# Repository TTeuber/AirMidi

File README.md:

# AirMidi

A battery-powered wireless MIDI interface: it gives any TRS MIDI device (or DIN, with an adapter) Bluetooth and Wi-Fi,
is set up from a browser or a phone, and updates itself over the air. This repo is its firmware, for an ESP32-C6 or
ESP32-S3 on a custom PCB in a 3D-printed box, and the apps that play it: one for Android phones and one for the Mac,
which sequences hardware synths through the box.

## Highlights

- **Six MIDI transports through one router**: TRS (31250 baud UART), BLE MIDI (peripheral and central), Network
  MIDI 2.0, RTP-MIDI, USB MIDI and an ESP-NOW link between two boxes. Everything is UMP (MIDI 2.0's packet format)
  inside, translated to and from MIDI 1.0 at the edges, with a per-output merge that never breaks a SysEx message.
- **Protocols built from their specs and tested against real implementations**: macOS's own Network MIDI 2.0 and
  RTP-MIDI drivers connect to the box; the RTP-MIDI recovery journal (RFC 6295) repairs lost packets; MIDI-CI
  Property Exchange reads a synth's controls over a 31250 baud cable and the web UI draws them.
- **A portable C11 core** (`lib/`, no ESP-IDF headers) with 17 suites of host tests under AddressSanitizer and
  UndefinedBehaviorSanitizer, including property tests (the journal through 30-50% packet loss).
- **Measured on the hardware, not assumed**: an audio interface cabled to the box's jacks puts both ends of every
  test on the Mac's clock, so latency and loss are measured one way, per transport. Every number below comes from
  those tests.
- **Safe updates**: signed images (RSA-3072), a self-test after each update and automatic rollback, core dumps
  from crashes; releases are built and signed in GitHub Actions.
- **Apps for phone and desktop** from one Flutter project: an Android app that sets the box up over Bluetooth and
  plays it as an MPE instrument, and a macOS app with a MIDI-only DAW for hardware synths, whose tracks know each
  synth's controls from what it sent over MIDI-CI.

## Hardware

The receiver PCB: a Seeed XIAO ESP32-C6 (or ESP32-S3) on headers, MIDI out through a TRS Type A jack, MIDI in
through a 6N138 optocoupler, a Li-ion cell with a TP4057 USB-C charger and a TPS63020 buck-boost to 3.3 V, a power
switch, a button and an LED. An ESP32-S3-DevKitC-1 serves as the second box for USB MIDI and the ESP-NOW link. The
board layer ([board-and-settings.md](docs/design/board-and-settings.md)) is the only code that names a GPIO.

**[hardware/](hardware)** has the schematic, the KiCad project, Gerbers, BOM and the printable enclosure, with the
board's revision history: the photo shows rev A, and rev B fixes what its bring-up found.

### The rev B panel

| button | tap | hold 2 s (its LED lights when you can let go) |
|---|---|---|
| BLE (blue) | Play mode: BLE + TRS | open the pairing window for a new phone (2 min) |
| NET (green) | Network mode | check GitHub for a newer release, install it |
| STP (yellow) | Setup mode; again: back to the mode before | MIDI-CI scan of the device on the jacks |
| PWR (red) | the four LEDs show the battery for 3 s | off (deep sleep); hold 1 s to start again |

Two quick taps on any button: all notes off, at the second tap. A hold that needs the other mode switches first
(with the restart a BLE change takes), then does its job. The LEDs: BLE flashes once a second while advertising, is
on when connected (dark flicker on MIDI), blinks fast while the pairing window for a new phone is open (it closes
once a phone is added; the one after power-on also closes when a trusted phone connects, and never blinks over a
connection); NET blinks while joining,
is dim when joined and on with a session, blinks fast while checking or installing, then shows the result (on: up
to date, three flashes: failed); STP double-flashes in Setup, blinks dim during a scan, then on (found) or three
flashes (nothing); PWR is on, triple-flashes on a low cell. The battery bar is a quarter per LED; with the switch
off on USB (no cell reading) all four blink.

## Features

- **TRS <-> BLE MIDI**, up to two BLE centrals at once. One way through the box: BLE -> TRS 8.4 ms median,
  TRS -> BLE 9.5 ms, nothing lost in the hardware tests.
- **Wi-Fi modes**: Play (Wi-Fi off), Network (joins stored networks, reachable as `<name>.local`), Setup (its own
  access point). A long press switches mode, an 8 s press opens Setup, a double press sends all notes off. Rev B
  has a panel instead: a button per mode (BLE, NET, STP) and PWR, each with an LED over it (below).
- **Web UI** at `http://<name>.local`: live traffic per port, battery, signal, settings, Wi-Fi networks, firmware
  updates. Plain JS, no framework, 18 KB, built into the firmware.
- **Network MIDI 2.0** host (UDP, `_midi2._udp`): macOS connects to it natively. FEC, retransmit and in-order
  delivery over Wi-Fi: 0 of 600 lost at 5 ms spacing, 6.7 ms median Mac -> TRS, 4.2 ms back.
- **MIDI-CI over TRS**: Discovery and Property Exchange with the synth on the jacks (a full read in under a second
  at 31250 baud, ~50 ms for a known device from the flash cache). The play page draws the synth's own faders,
  pickers and toggles from its control list (M2-117); synths without MIDI-CI get the same from an uploaded JSON
  profile. A MIDI-CI host behind the box reaches the synth through it: macOS finds it over Network MIDI 2.0.
- **RTP-MIDI** (AppleMIDI, `_apple-midi._udp`) for clients without Network MIDI 2.0: lost packets repaired from the
  recovery journal, sessions taken back after the box restarts. With macOS's driver: 0 of 600 lost each way at 5 ms
  spacing, 7.3 / 5.5 ms median.
- **BLE central**: the box connects by itself to a BLE MIDI keyboard or controller (any, by name or by address).
  13.0 ms median keyboard -> TRS.
- **USB MIDI** on the S3: a class-compliant USB MIDI device named after the box, with a serial console beside it.
- **ESP-NOW link**: two boxes pass MIDI radio to radio, no router, and find each other's Wi-Fi channel by
  themselves. TRS -> box -> ESP-NOW -> box -> USB in 3.8 ms median, nothing lost.
- **Updates**: upload in the browser, fetch the latest GitHub release, or send it over BLE when the box is not on
  Wi-Fi. Only signed images install; a new image must pass a self-test or the box rolls back.
- **Battery**: gauge, low warning, and all notes off plus deep sleep when the cell is empty.

## Web UI

## Apps

One Flutter project ([app/](app)) builds two apps over shared code: the box pages, the BLE and Wi-Fi links, and the
synth page drawn from the synth's MIDI-CI control list.

**Phone** (Android; [plan and decisions](docs/app.md)):

- Finds the box over Bluetooth or Wi-Fi and sets it up: mode, Wi-Fi networks from the box's own scan, trusted
  phones. Setup goes over a BLE GATT service that carries the same JSON API as the web UI's HTTP.
- Plays the synth on the box's TRS jacks: pedal-steel strips (each finger bends its own note, one MPE channel per
  strip), keys, or drum pads; over BLE MIDI, the box's WebSocket, or Android's MIDI service straight to a computer.
- The synth page: envelopes, a cutoff and resonance pad, wave pickers and faders, built from the controls daisy_synth
  ([devices/daisy_synth](devices/daisy_synth)) describes over MIDI-CI.

**Desktop** (macOS now, Windows and Linux later; [plan](docs/desktop.md), [DAW design](docs/daw.md)):

- The computer's MIDI ports through libremidi over FFI (`app/packages/midi_engine`), a router between them, and the
  box's play view: the synth's controls over the keys.
- A MIDI-only DAW for hardware: MIDI clips in a piano roll with controller lanes and ramps, MPE takes with each
  note's own bend, pressure and timbre, and step-sequencer patterns with velocity, gate, probability, nudge, repeats
  and parameter locks. Records from any input, MPE included.
- Each track keeps its synth's MIDI-CI control list, so lanes and locks have the synth's own names and units. It also
  keeps the synth's program, bank and settings, which can be read back through the box. All of it is sent before
  play, so the song sounds the same on the next day.
- Click and count-in, latency offsets per port, projects saved as JSON every few seconds, Standard MIDI File import
  and export.

## How it is tested

- **Host tests** (`test/`): the portable core under ASan + UBSan, with randomized round trips and property tests.
- **App tests** (`app/test`, `fvm flutter test`): the strips, MPE and BLE MIDI packing, the router, and the DAW (editing,
  timing, files, recording, the player against a fake MIDI engine).
- **CI** (`.github/workflows/ci.yml`): host tests, the clang-format check, the firmware for every board, and the
  app's analyzer, tests and Android and Mac release builds on every push. `tools/check.sh` runs the same steps locally. Tagging `vX.Y.Z` builds, signs and publishes a release.
- **Hardware in the loop** (`tools/hil/`): Python and Swift tools on the Mac drive the box and an Arturia AudioFuse
  wired to its jacks. Their first runs found real bugs; each one is written up in [docs/design](docs/design).

| Test | Checks |
|---|---|
| `bridge_test.py` | TRS <-> BLE both ways: notes, CCs on all 16 channels, clock, long SysEx, bursts, two sources merged (15) |
| `ota_test.py`, `release_test.py`, `ble_ota_test.py` | unsigned, corrupted and wrongly signed images refused; good ones installed over Wi-Fi, from a release and over BLE; rollback after a failed self-test or a crash (13, 8, 9) |
| `web_test.py`, `ws_test.py` | the web API, and MIDI between the page and the jacks over WebSocket (14) |
| `ci_test.py`, `mac_ci_test.py` | MIDI-CI against a stand-in synth on the Mac, and macOS's own MIDI-CI through the box (21, 12) |
| `resume_test.py`, `rtp_test.py` | Network MIDI 2.0 and RTP-MIDI against macOS's drivers: loss, latency, box restarts (14, 13) |
| `central_test.py` | the box as BLE central against a BLE MIDI stand-in on the Mac (14) |
| `usb_test.py`, `espnow_test.py` | USB MIDI against BLE, and two boxes linked over ESP-NOW (9) |
| `latency.py`, `sleep_test.py` | one-way latency per path, MIDI through each power mode |

## Design notes

One note per module, with the reasoning, the alternatives considered and what the hardware tests found:

- [core.md](docs/design/core.md): UMP, MIDI 1.0 parsing and encoding, MIDI 1.0 <-> 2.0 translation
- [transports.md](docs/design/transports.md): the bus and merge, TRS, BLE MIDI, BLE central, USB MIDI, ESP-NOW, power
- [network-midi.md](docs/design/network-midi.md): Network MIDI 2.0
- [rtp-midi.md](docs/design/rtp-midi.md): RTP-MIDI, the recovery journal, and what macOS needed
- [midi-ci.md](docs/design/midi-ci.md): MIDI-CI Discovery and Property Exchange, the generated play page
- [ota.md](docs/design/ota.md): flash layout, signed updates, self-test and rollback, releases
- [board-and-settings.md](docs/design/board-and-settings.md): the board layer and the settings store
- [config-over-ble.md](docs/design/config-over-ble.md): one JSON API for HTTP and BLE, trusted phones, Wi-Fi setup from a phone
- [testing.md](docs/design/testing.md): the test rig and CI
- [measurements.md](docs/measurements.md): every number in this README, with its method
- [plan.md](docs/plan.md): the development plan and a decision log of every choice and measured result
- [app.md](docs/app.md): the Android app (`app/`): plan, phases and its decision log
- [desktop.md](docs/desktop.md): the desktop app (plan): MIDI engine, router, who keeps time; [daw.md](docs/daw.md): the DAW
- [system](docs/system/README.md): how the box, the app and future instruments fit together: tiers, links, the instrument checklist

## Layout

```
lib/        portable C11 core, no ESP-IDF headers         docs/design/  one note per module
test/       host unit tests for lib/ (Unity)              tools/hil/    hardware-in-the-loop tools for the Mac
firmware/   ESP-IDF project (C6 and S3)                   spikes/       early experiments, results in the plan
web/        the web UI (HTML/CSS/JS, gzipped into the firmware)
devices/    MIDI-CI device side: the Mac stand-in (CoreMIDI) and daisy_synth, the demo synth
hardware/   the receiver PCB and enclosure: schematic, KiCad project, Gerbers, BOM, STL
app/        Flutter: the Android app, the macOS app with the DAW, and the code they share
```

## Build

```sh
tools/check.sh                    # what CI runs: host tests, clang-format check, firmware for every board
firmware/build.sh c6 flash        # build and flash the C6 board (s3: XIAO S3 on rev A, s3b: on rev B, s3kit: S3 dev kit)
cd app && fvm flutter test        # the apps' tests (Flutter pinned in app/.fvmrc)
fvm flutter build apk --release   # the Android app (fvm flutter build macos --release for the Mac)
```

Needs ESP-IDF v5.5.5 or later in the v5.5 series (`IDF_PATH`, default `~/Developer/esp-idf`), CMake, and `uv` (for
the pinned clang-format and the Python test tools). Each [release](https://github.com/TTeuber/AirMidi/releases) has
the update image per board and a zip for a first install over USB (`esptool.py write_flash @flash_args`).

## License

The firmware, software and documentation are MIT ([LICENSE](LICENSE)); the hardware in `hardware/` is
CERN-OHL-P-2.0 ([hardware/LICENSE](hardware/LICENSE)), the permissive open hardware licence. Two bundled third-party
parts keep their own licenses: the Unity test framework in `test/unity/` (MIT,
[test/unity/LICENSE.txt](test/unity/LICENSE.txt)) and the Geist font in `web/` (SIL Open Font License 1.1,
[web/OFL-Geist.txt](web/OFL-Geist.txt)).

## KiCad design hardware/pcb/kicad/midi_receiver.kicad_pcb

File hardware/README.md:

# Hardware: the AirMidi receiver, rev B

A 72 x 46 mm two-layer board for a Seeed XIAO ESP32-C6 or ESP32-S3, in an 80 x 52 x 27 mm 3D-printed box. The
photo shows rev A, the board the firmware was developed and tested on; this folder is rev B, which fixes rev A's
mistakes (see [Revisions](#revisions)).

The schematic, board and enclosure are generated from code (a Python circuit description, a layout file and a
build123d enclosure script) in a separate design workspace. The files here are that workspace's outputs, copied in by
an export script: they are replaced on every export, so edit the design there, not here.

## What's here

| Path | Contents |
|---|---|
| [pcb/schematic.pdf](pcb/schematic.pdf) | the schematic |
| [pcb/board.pdf](pcb/board.pdf), [pcb/board_3d.png](pcb/board_3d.png), [pcb/board_3d_bottom.png](pcb/board_3d_bottom.png) | the board: copper, silkscreen, 3D renders |
| [pcb/erc.txt](pcb/erc.txt), [pcb/drc.txt](pcb/drc.txt) | electrical and design rule checks: 0 errors, 0 unconnected, schematic and board in step |
| [pcb/kicad/](pcb/kicad) | the KiCad 10 project, with the symbols, footprints and 3D models it needs beyond KiCad's own library in `kicad/lib/` |
| [fab/midi_receiver_gerbers.zip](fab/midi_receiver_gerbers.zip) | Gerbers and Excellon drill file, as uploaded to JLCPCB (any 2-layer fab takes them) |
| [fab/bom.csv](fab/bom.csv) | every part, including the ones without a footprint (cell, screws) |
| [fab/bom_jlcpcb.csv](fab/bom_jlcpcb.csv), [fab/cpl_jlcpcb.csv](fab/cpl_jlcpcb.csv) | JLCPCB's BOM and placement formats |
| [enclosure/base.stl](enclosure/base.stl), [enclosure/lid.stl](enclosure/lid.stl) | the box, ready to slice (GitHub shows them in 3D); STEP files beside them |
| [enclosure/assembly_views.png](enclosure/assembly_views.png) | the board and every part inside the closed box |

The 3D models of the LCSC parts (TRS jacks, optocoupler, slide switch) are not included, as their license terms are
unclear; KiCad's 3D viewer shows those parts as bare footprints. The renders above were made with them.

## Circuit

```
phone / DAW  <~~ BLE MIDI, Wi-Fi ~~>  XIAO ESP32-C6 / S3  --UART TX--> 10R / 33R current loop --> J2 TRS out --> synth
                                            ^
keyboard --> J3 TRS in --> 220R + 1N4148 --> 6N138 optocoupler, 1k pull-up --UART RX

USB-C --> TP4057 charger module --> Li-ion cell 1050 mAh (J1) --> SW1 --> TPS63020 buck-boost --> 3.3 V --> XIAO 3V3
                                                                       '--> 100k / 100k divider --> A0 (battery gauge)
```

- **MIDI out**: a 3.3 V current loop (10 ohm on the source side, 33 ohm on the data side) to a TRS Type A jack:
  tip = DIN pin 5, ring = DIN pin 4.
- **MIDI in**: the MIDI spec's opto-isolated input with a 6N138: 220 ohm and a reverse 1N4148 on its LED, 1k pull-up
  to 3.3 V on its output.
- **Power**: the cell feeds a TP4057 charger module (USB-C, 500 mA) and, through the power switch, a TPS63020
  buck-boost that makes 3.3 V over the cell's whole range. Both are modules on header pins. The XIAO runs from its
  3V3 pin, so the switch must be off before the XIAO's own USB is plugged in.
- **User interface**: a status LED and a 13 mm tactile button that reach through the lid.

| Signal | XIAO pin | C6 GPIO | S3 GPIO |
|---|---|---|---|
| MIDI TX -> J2 | D6 | 16 | 43 |
| MIDI RX <- J3 | D7 | 17 | 44 |
| Battery sense | A0 | 0 | 1 |
| Status LED | D1 | 1 | 2 |
| Button (to GND) | D2 | 2 | 3 |

## Enclosure

Two parts that print without supports: the base, with a pocket for the cell under the board, and a flat lid. Four
M3 x 20 screws go through the lid and the board into the base. The jacks sit flush in the front wall, the power
switch's handle comes through a slot in the right wall, and both USB-C ports (charging, and the XIAO for flashing)
face the back.

## Measured on rev A

| What | Result |
|---|---|
| MIDI loopback J2 -> J3 at 31250 baud | 30208 of 30208 bytes correct; still clean at 62500 baud (2x headroom) |
| XIAO current, BLE connected | 40-50 mA |
| Battery gauge vs a multimeter | 3.726 V vs 3.74 V |
| Radio, ceramic antenna, box closed | BLE advertisement at the Mac -42 dBm, connection -50 dBm |
| Latency and loss through the box | in the firmware's [measurements](../docs/measurements.md) |

## Revisions

**Rev A** (ordered 2026-09-22, built 2026-10-03; the board in the photo):

- **Battery connector reversed.** JST-PH battery plugs have no standard polarity: the footprint put + on pin 1, but
  the cell's plug has its red lead on pin 2. Plugged in for the first time, the reversed cell destroyed the TP4057
  charger module. Lesson: check every cell's lead colours against the footprint's pad numbers before ordering.
- **Garbage on MIDI OUT at reset.** D6/D7 are the module's UART0 pins, and the chip's ROM bootloader prints its boot
  banner on UART0 TX before any firmware runs, which a synth reads as random MIDI messages. Fixed without a new
  board: one eFuse (`UART_PRINT_CONTROL`) silences the ROM output, and the firmware drives MIDI from UART1 routed to
  those pins ([board-and-settings.md](../docs/design/board-and-settings.md)).
- **An ESP32-C6 instead of the planned S3** (the S3s were back-ordered). The XIAO modules share a pinout, so the
  board did not change; the firmware's board layer maps the GPIOs. (The footprint keeps its `XIAO_ESP32S3` name.)
- **Enclosure too low** for the leads the hand-soldered parts leave under the board.

**Rev B** (this folder; not built yet): the cell connector's pins swapped to match the cell; the enclosure with 6 mm
under the board for those leads (27 mm tall overall), the cell pocket moved against the jack wall, and a gap in a
rib for the cell's lead.

## License

[CERN-OHL-P-2.0](LICENSE) (CERN Open Hardware Licence, permissive), for everything in this folder. The firmware and
the rest of the repository are MIT.

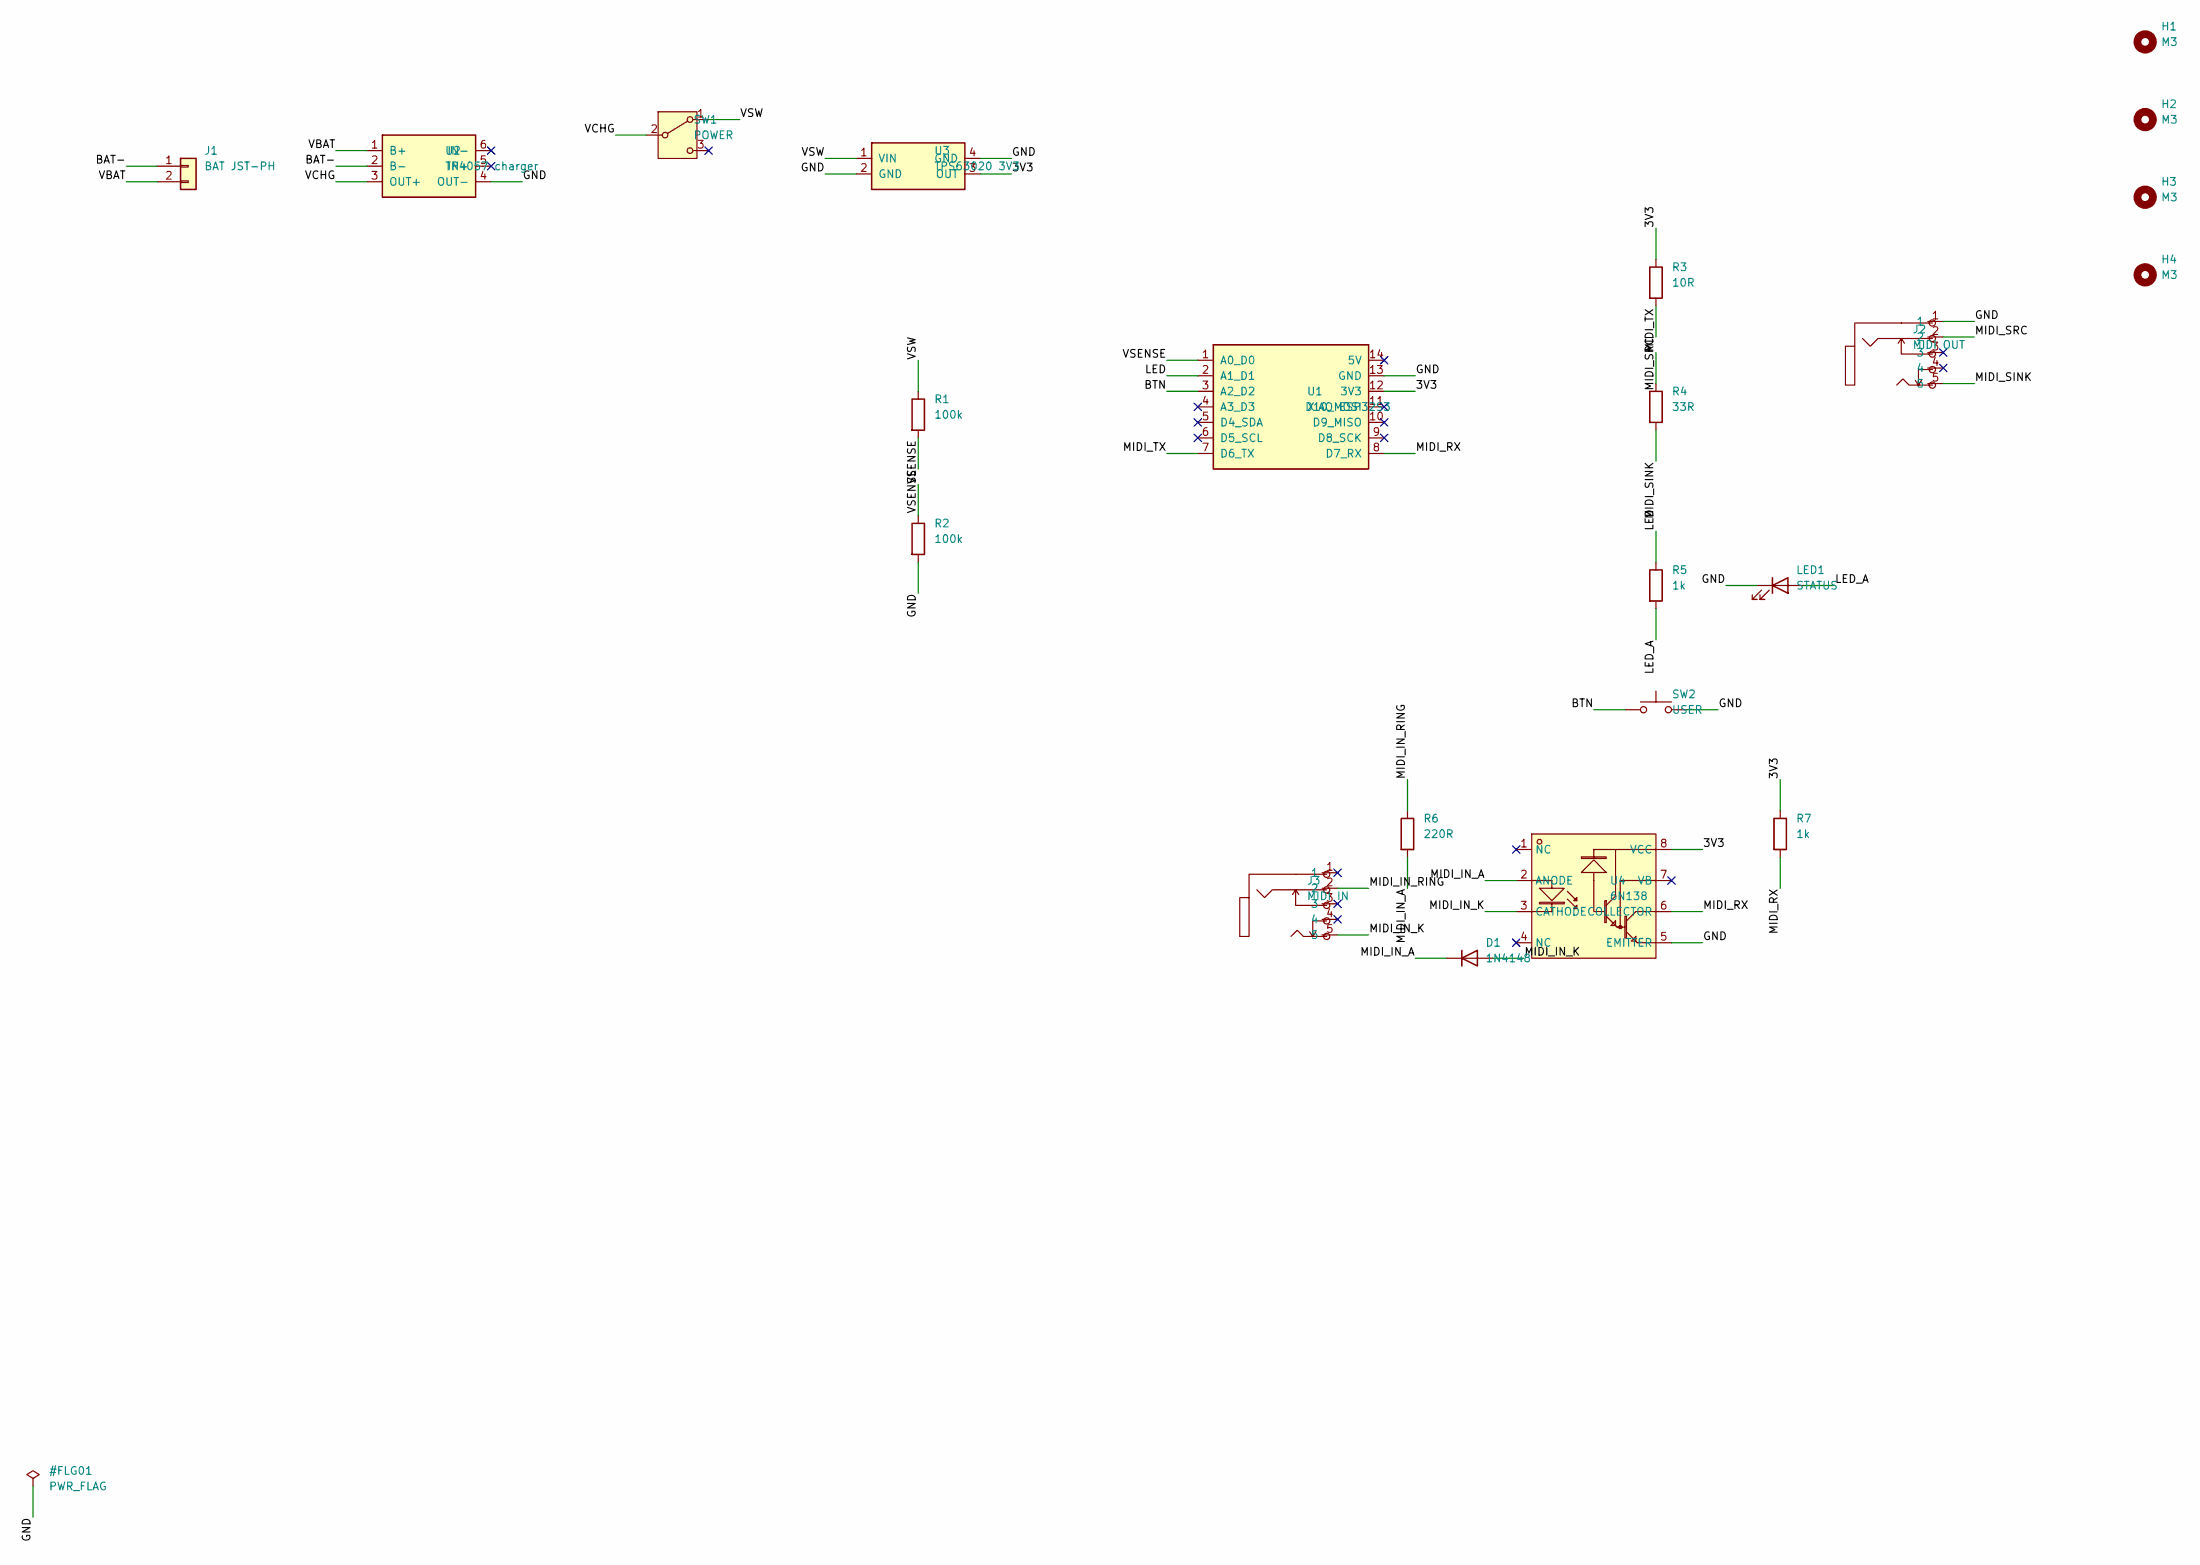
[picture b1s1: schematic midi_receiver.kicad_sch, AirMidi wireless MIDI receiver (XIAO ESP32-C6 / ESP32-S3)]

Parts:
D1: 1N4148; D_DO-35_SOD27_P7.62mm_Horizontal
H1, H2, H3, H4: M3; MountingHole_3.2mm_M3
J1: BAT JST-PH; JST_PH_S2B-PH-K_1x02_P2.00mm_Horizontal
J2: MIDI OUT; AUDIO-TH_PJ307C
J3: MIDI IN; AUDIO-TH_PJ307C
LED1: STATUS; LED_D3.0mm
R1, R2: 100k; R_Axial_DIN0207_L6.3mm_D2.5mm_P7.62mm_Horizontal
R3: 10R; R_Axial_DIN0207_L6.3mm_D2.5mm_P7.62mm_Horizontal
R4: 33R; R_Axial_DIN0207_L6.3mm_D2.5mm_P7.62mm_Horizontal
R5, R7: 1k; R_Axial_DIN0207_L6.3mm_D2.5mm_P7.62mm_Horizontal
R6: 220R; R_Axial_DIN0207_L6.3mm_D2.5mm_P7.62mm_Horizontal
SW1: POWER; SW-TH_3P-P4.80_HX-SS12D10G6-WJ
SW2: USER; SW_PUSH_6mm_H13mm
U1: XIAO ESP32S3; XIAO_ESP32S3
U2: TP4057 charger; TP4057_Module
U3: TPS63020 3V3; TPS63020_Module
U4: 6N138; DIP-8_W7.62mm_Socket

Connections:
/3V3: R3.1, R7.1, U1.12 (3V3), U3.3 (OUT), U4.8 (VCC)
/BAT-: J1.1, U2.2 (B-)
/BTN: SW2.1, U1.3 (A2_D2)
/GND: J2.1, LED1.1 (K), R2.2, SW2.2, U1.13 (GND), U2.4 (OUT-), U3.2 (GND), U3.4 (GND), U4.5 (EMITTER)
/LED: R5.1, U1.2 (A1_D1)
/LED_A: LED1.2 (A), R5.2
/MIDI_IN_A: D1.1 (K), R6.2, U4.2 (ANODE)
/MIDI_IN_K: D1.2 (A), J3.5, U4.3 (CATHODE)
/MIDI_IN_RING: J3.2, R6.1
/MIDI_RX: R7.2, U1.8 (D7_RX), U4.6 (COLLECTOR)
/MIDI_SINK: J2.5, R4.2
/MIDI_SRC: J2.2, R3.2
/MIDI_TX: R4.1, U1.7 (D6_TX)
/VBAT: J1.2, U2.1 (B+)
/VCHG: SW1.2 (B), U2.3 (OUT+)
/VSENSE: R1.2, R2.1, U1.1 (A0_D0)
/VSW: R1.1, SW1.1 (A), U3.1 (VIN)

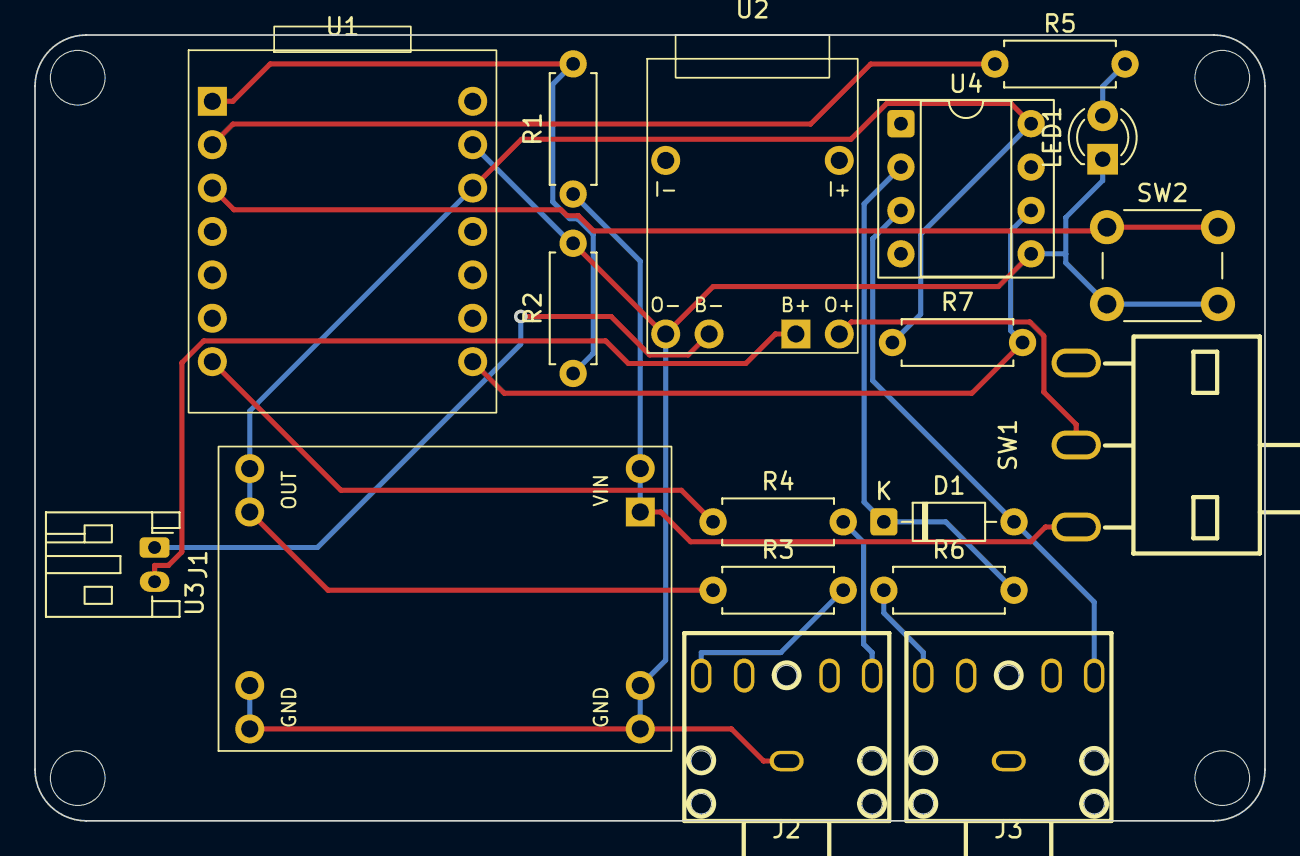
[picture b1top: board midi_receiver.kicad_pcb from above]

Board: 2 copper layers, 72.0 x 46.0 mm, 22 parts (0 on the bottom side), 17 nets.

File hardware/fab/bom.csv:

qty,refs,description,MPN,LCSC
1,U1,Seeed XIAO ESP32S3 soldered straight onto the board on its male headers (no sockets),XIAO ESP32S3,C2913204
1,U2,"TP4057 USB-C Li-ion charger module with protection, 12.1 x 17 mm, soldered on header stubs",TP4057 USB-C module,
1,U3,"TPS63020 buck-boost module, 1.8-5.5 V in, 3.3 V out, 17.6 x 26.3 mm, soldered on header stubs",TPS63020 module,
1,J1,"JST S2B-PH-K-S, 2-pin PH 2.0 mm side-entry socket (Li-ion cell plug)",S2B-PH-K-S(LF)(SN),C173752
2,J2 J3,"3.5 mm stereo jack, right angle PCB mount, 5 pins (PJ-307C) for TRS MIDI",PJ-307C,C16684
1,U4,"6N138 darlington optocoupler, DIP-8, in a socket (MIDI in)",6N138,C3001991
1,SW1,"SPDT slide switch, right angle (bent pins), 4.8 mm pitch, 12.7 x 6.2 x 6.5 body, 6 mm handle (SS12D10G6-WJ)",SS12D10G6-WJ,C7431059
1,SW2,"6 mm tactile button, 13 mm tall round stem (user button through a flat lid)",KH-6X6X13H-TJ,C2837523
1,D1,"1N4148 small signal diode, DO-35, lying flat on 7.62 mm (MIDI in reverse protection)",1N4148,
1,LED1,"3 mm LED, green (BLE status)",3A4GUD,C52034646
2,R1 R2,"100 kOhm 1/4 W resistor, flat (battery-sense divider)",,
1,R3,"10 Ohm 1/4 W resistor, flat (MIDI out source side)",,
1,R4,"33 Ohm 1/4 W resistor, flat (MIDI out data side)",,
2,R5 R7,"1 kOhm 1/4 W resistor, flat (LED series)",,
1,R6,"220 Ohm 1/4 W resistor, flat (MIDI in LED series)",,
4,H1 H2 H3 H4,M3 mounting hole,,
1,,"EEMB LP553454 Li-Po cell, 3.7 V 1050 mAh, 54x34x5 mm, JST-PH 2.0 plug, built-in protection (PCM)",LP553454,
7,,1x2 2.54 mm pin header (footswitch leads),,
1,,"DIP-8 IC socket, 7.62 mm",DS1009-08AT1NX-0A2,C72124
4,,M3 x 20 mm pan head screw (receiver lid through the boss and PCB into the base standoff),,

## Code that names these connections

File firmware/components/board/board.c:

#include "board.h"

#include <stdio.h>

#include "driver/gpio.h"
#include "esp_mac.h"
#include "sdkconfig.h"

#if CONFIG_AIRMIDI_BOARD_XIAO_C6
static const board_t the_board = {
    .name = "receiver rev A + XIAO ESP32-C6",
    .midi_tx = GPIO_NUM_16,
    .midi_rx = GPIO_NUM_17,
    .led = GPIO_NUM_1,
    .button = GPIO_NUM_2,
    .batt_adc_unit = ADC_UNIT_1,
    .batt_adc_channel = ADC_CHANNEL_0,  // GPIO0
    .batt_offset_mv = 14,               // board #1: calibrated ADC read 14 mV under the meter (2026-10-05)
};
// Inside the XIAO C6 module: GPIO3 low powers the RF switch, GPIO14 low selects the ceramic antenna (high = the
// U.FL connector, measured ~20 dB weaker with nothing plugged in).
#define RF_SWITCH_EN GPIO_NUM_3
#define ANT_SELECT GPIO_NUM_14
#elif CONFIG_AIRMIDI_BOARD_XIAO_S3
static const board_t the_board = {
    .name = "receiver rev A + XIAO ESP32-S3",
    .midi_tx = GPIO_NUM_43,
    .midi_rx = GPIO_NUM_44,
    .led = GPIO_NUM_2,
    .button = GPIO_NUM_3,
    .batt_adc_unit = ADC_UNIT_1,
    .batt_adc_channel = ADC_CHANNEL_0,  // GPIO1
};
#elif CONFIG_AIRMIDI_BOARD_XIAO_S3_B
// pcb/midi_receiver/circuit.py PANEL in the design workspace: LEDs A1 A3 SDA SCL, buttons SCK MISO MOSI A2.
static const board_t the_board = {
    .name = "receiver rev B + XIAO ESP32-S3",
    .midi_tx = GPIO_NUM_43,
    .midi_rx = GPIO_NUM_44,  // H11L1 output, 270R pull-up
    .led = GPIO_NUM_NC,
    .button = GPIO_NUM_NC,
    .panel = true,
    .panel_led = {GPIO_NUM_2, GPIO_NUM_4, GPIO_NUM_5, GPIO_NUM_6},  // as built: blue, green (2k), yellow, orange (1k)
    .panel_button = {GPIO_NUM_7, GPIO_NUM_8, GPIO_NUM_9, GPIO_NUM_3},
    .panel_led_max = {25, 25, 100, 35},  // all too bright at full duty, and yellow a little dim against the rest
    .batt_adc_unit = ADC_UNIT_1,
    .batt_adc_channel = ADC_CHANNEL_0,  // GPIO1
};
#elif CONFIG_AIRMIDI_BOARD_REV_C
// pcb/midi_receiver_c/circuit.py in the design workspace. MIDI TX is off UART0's pin, so the ROM's boot log stays out
// of the MIDI output, and off the pins Espressif lists with a power-up glitch; TX and RX stay off VDD_SPI's GPIO33-37.
static const board_t the_board = {
    .name = "receiver rev C",
    .midi_tx = GPIO_NUM_38,
    .midi_rx = GPIO_NUM_39,  // H11L1 output, 270R pull-up, on the switched supply
    .led = GPIO_NUM_NC,
    .button = GPIO_NUM_NC,
    .panel = true,
    // blue, green (10k), yellow (1.5k), orange (3.3k)
    .panel_led = {GPIO_NUM_11, GPIO_NUM_13, GPIO_NUM_15, GPIO_NUM_17},
    .panel_button = {GPIO_NUM_12, GPIO_NUM_14, GPIO_NUM_16, GPIO_NUM_18},
    // rev B's judged levels scaled to these resistors: confirm on the first board
    .panel_led_max = {100, 100, 150, 110},
    .batt_adc_unit = ADC_UNIT_1,
    .batt_adc_channel = ADC_CHANNEL_9,  // GPIO10
    .opto_en = GPIO_NUM_40,
    .vbus_sense = GPIO_NUM_21,
};
#elif CONFIG_AIRMIDI_BOARD_DEVKITC_S3
static const board_t the_board = {
    .name = "ESP32-S3-DevKitC-1",
    .midi_tx = GPIO_NUM_17,  // free pins (43/44 go to the kit's USB-UART bridge)
    .midi_rx = GPIO_NUM_18,
    .led = GPIO_NUM_NC,    // only an addressable RGB LED on the kit
    .button = GPIO_NUM_0,  // BOOT, with the kit's pull-up
    .batt_adc_unit = ADC_UNIT_1,
    .batt_adc_channel = -1,  // no battery: always "on USB"
    // At the full 20 dBm none of the kit's Wi-Fi frames arrived (no ESP-NOW acknowledgement, no access point
    // answering its authentication) while BLE worked; at 10 dBm all did. Most likely its 3.3 V sagging at the
    // transmit peaks on a USB port.
    .wifi_max_tx = 60,
};
#else
#error "no board selected (CONFIG_AIRMIDI_BOARD)"
#endif

const board_t *board(void) { return &the_board; }

void board_init(void) {
#ifdef RF_SWITCH_EN
    gpio_config_t rf = {.pin_bit_mask = 1ULL << RF_SWITCH_EN | 1ULL << ANT_SELECT, .mode = GPIO_MODE_OUTPUT};
    gpio_config(&rf);
    gpio_set_level(RF_SWITCH_EN, 0);
    gpio_set_level(ANT_SELECT, 0);
#endif
    // before the UART looks at its line; the pin floats in deep sleep and a pull-up turns it off
    if (the_board.opto_en) {
        gpio_config_t en = {.pin_bit_mask = 1ULL << the_board.opto_en, .mode = GPIO_MODE_OUTPUT};
        gpio_config(&en);
        gpio_set_level(the_board.opto_en, 0);
    }
    if (the_board.led != GPIO_NUM_NC) {
        gpio_config_t led = {.pin_bit_mask = 1ULL << the_board.led, .mode = GPIO_MODE_OUTPUT};
        gpio_config(&led);
        gpio_set_level(the_board.led, 0);
    }
    if (the_board.button != GPIO_NUM_NC) {
        gpio_config_t btn = {
            .pin_bit_mask = 1ULL << the_board.button, .mode = GPIO_MODE_INPUT, .pull_up_en = GPIO_PULLUP_ENABLE};
        gpio_config(&btn);
    }
}

// The Wi-Fi station MAC's last three bytes. (Not the default MAC: on the C6 that reads as the 8-byte EUI-64 of its
// 802.15.4 radio, ff:fe in the middle.) 8 bytes of buffer all the same, for any chip that writes more.
void board_id_bytes(uint8_t out[3]) {
    uint8_t mac[8] = {0};
    esp_read_mac(mac, ESP_MAC_WIFI_STA);
    out[0] = mac[3], out[1] = mac[4], out[2] = mac[5];
}

const char *board_id(void) {
    static char id[7];
    if (!id[0]) {
        uint8_t b[3];
        board_id_bytes(b);
        snprintf(id, sizeof id, "%02x%02x%02x", b[0], b[1], b[2]);
    }
    return id;
}

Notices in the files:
README.md:
License: MIT
